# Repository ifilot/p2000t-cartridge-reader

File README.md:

# P2000T Cartridge Reader

This repository contains hard- and software utilities to read P2000T cartridges
using an [Arduino Leonardo](https://docs.arduino.cc/hardware/leonardo) board.
The repository is organized as follows. The [arduino](arduino) folder contains
the source code for the Arduino Leonardo. In the [kicad](kicad) folder the
files can be found for the arduino shield board. Finally, in the [script](scripts)
folder a number of Python scripts can be found interfacing with the Arduino
Leonardo board to dump cartridge roms to a file.

## Kicad scheme

## Uploading the firmware

Open the [Arduino IDE](https://www.arduino.cc/en/software) and open the file
`cartridge_reader_firmware.ino`. Verify that the source code can be correctly
compiled and upload it to the Arduino Leonardo. Next, proceed to the Python
files as found below. Test that the interface is functioning and then use
the `readrom.py` file to dump the cartridges.

## Python files

The following three Python files are provided to interface with the Arduino
Leonardo Board. To work with these files, you need to have the
[pyserial](https://pypi.org/project/pyserial/) package installed.

* [serialtest.py](scripts/serialtest.py): Tests whether Python can succesfully
  interface with the Arduino Leonardo and the cartridge reader firmware.
* [comparison_test.py](scripts/comparison_test.py): Tests whether the standard
  basic cartridge can be succesfully read. This requires one to have such a
  cartridge in their possession.
* [readrom.py](scripts/readrom.py): Dumps the contents of the cartridge in
  a `rom.bin` file. The `rom.bin` file is stored in the same folder as where
  this file resides.

## Logic table

In the table below, the interfacing of the Arduino pins to the signals on the
P2000T cartridge can be found. This interfacing scheme has been designed
around the documentation as found [here](https://www.philips-p2000t.nl/cartridges/basic-cartridge).
**It should be explicitly mentioned that the scheme as found in the Field Support
Manual is erroneous and has the CARSEL1 (CS1) and CARSEL2 (CS2) pins swapped.**

| BANK | D8 / A12B | D2 / ~CS1 | D3 / ~CS2 | A12  | A13  | ~CS  |
|------|-----------|-----------|-----------|------|------|------|
|`0x00`| HIGH      | LOW       | HIGH      | LOW  | LOW  | LOW  |
|`0x01`| LOW       | LOW       | HIGH      | HIGH | LOW  | LOW  |
|`0x02`| HIGH      | HIGH      | LOW       | LOW  | HIGH | LOW  |
|`0x03`| LOW       | HIGH      | LOW       | HIGH | HIGH | LOW  |
| N/A  | x         | HIGH      | HIGH      | x    | x    | HIGH |

## Bill of materials

* Arduino Leonardo
* 2x15 pin edge connector; pitch 3.96mm
* 74HCT4040N or similar

## Picture

## Licensing

* All source code, i.e. the [firmware](arduino/cartridge_reader_firmware) and the Python [scripts](scripts)
  are released under a [GPLv3 license](https://www.gnu.org/licenses/gpl-3.0.html).
* The hardware files to (re)produce the Arduino board are released under the 
  [CC BY-SA 4.0](https://creativecommons.org/licenses/by-sa/4.0/) license.

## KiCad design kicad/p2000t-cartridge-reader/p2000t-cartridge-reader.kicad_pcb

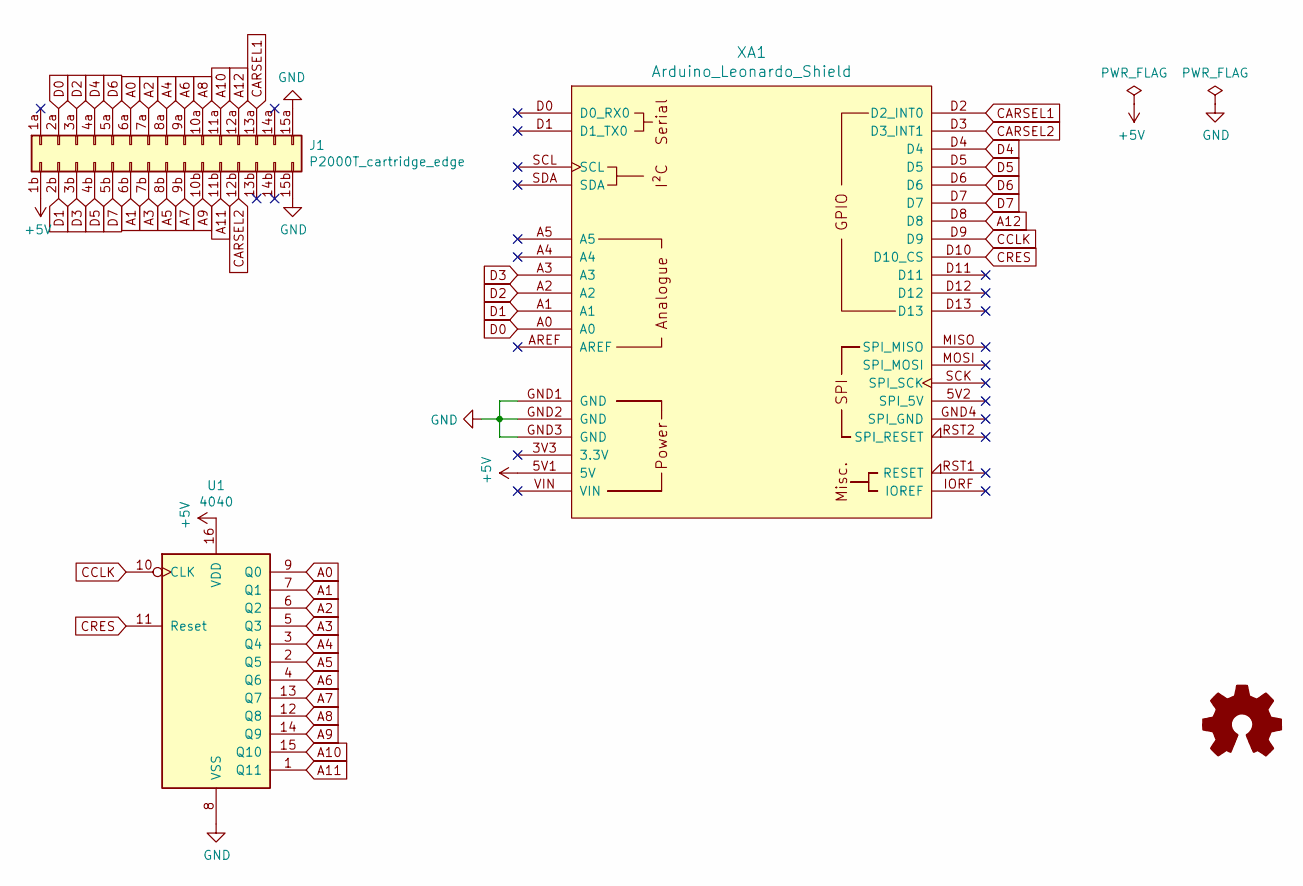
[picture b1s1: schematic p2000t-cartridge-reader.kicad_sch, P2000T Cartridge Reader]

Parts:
J1: P2000T_cartridge_edge; EdgeConnector2x15_no_screws
U1: 4040; DIP-16_W7.62mm_Socket
XA1: Arduino_Leonardo_Shield; Arduino_Uno_Shield

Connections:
+5V: J1.1b, U1.16 (VDD), XA1.5V1 (5V)
A0: J1.6a, U1.9 (Q0)
A1: J1.6b, U1.7 (Q1)
A2: J1.7a, U1.6 (Q2)
A3: J1.7b, U1.5 (Q3)
A4: J1.8a, U1.3 (Q4)
A5: J1.8b, U1.2 (Q5)
A6: J1.9a, U1.4 (Q6)
A7: J1.9b, U1.13 (Q7)
A8: J1.10a, U1.12 (Q8)
A9: J1.10b, U1.14 (Q9)
A10: J1.11a, U1.15 (Q10)
A11: J1.11b, U1.1 (Q11)
A12: J1.12a, XA1.D8
CARSEL1: J1.13a, XA1.D2 (D2_INT0)
CARSEL2: J1.12b, XA1.D3 (D3_INT1)
CCLK: U1.10 (CLK), XA1.D9
CRES: U1.11 (Reset), XA1.D10 (D10_CS)
D0: J1.2a, XA1.A0
D1: J1.2b, XA1.A1
D2: J1.3a, XA1.A2
D3: J1.3b, XA1.A3
D4: J1.4a, XA1.D4
D5: J1.4b, XA1.D5
D6: J1.5a, XA1.D6
D7: J1.5b, XA1.D7
GND: J1.15a, J1.15b, U1.8 (VSS), XA1.GND1 (GND), XA1.GND2 (GND), XA1.GND3 (GND)

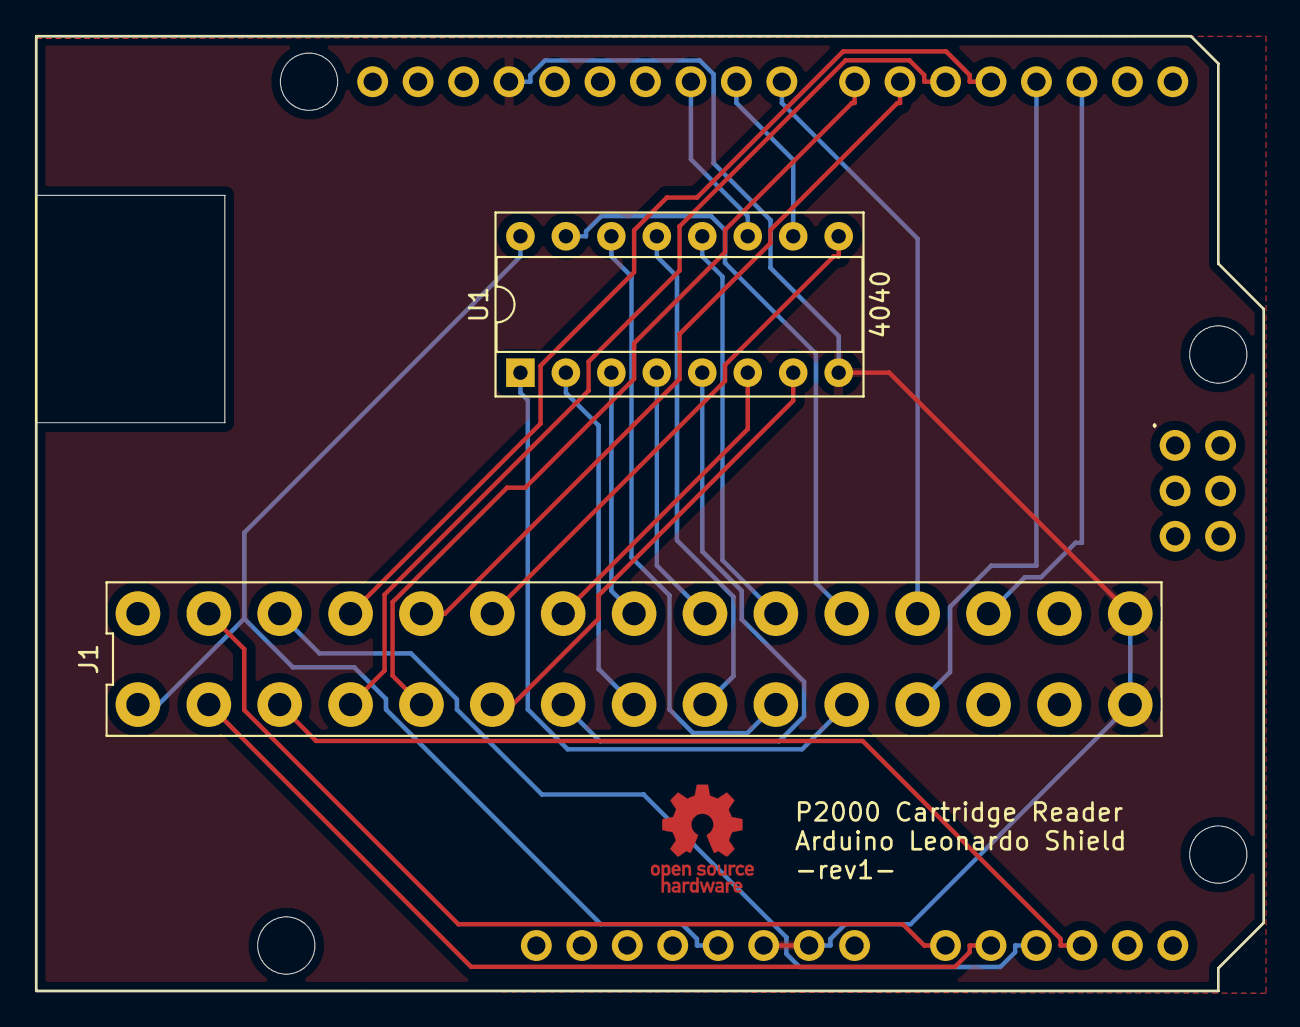
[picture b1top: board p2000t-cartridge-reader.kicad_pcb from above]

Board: 2 copper layers, 68.6 x 53.3 mm, 3 parts (0 on the bottom side), 27 nets.

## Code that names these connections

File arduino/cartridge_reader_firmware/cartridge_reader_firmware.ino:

/*
 * Note that there is an error in the Field Support Manual
 * 
 * CARSEL1 is on PIN 13A and CARSEL2 on PIN 12B; this is presented
 * reversed (incorrectly) in the FSM. See also:
 * https://www.philips-p2000t.nl/cartridges/basic-cartridge
 * 
 * Please note that this script only works for the P2000 Cartridge Reader
 * Boards __REV1__ and higher.
 */

#define ADDR_A12 8
#define ADDR_CARSEL1 2
#define ADDR_CARSEL2 3
#define CCLK 9
#define CRES 10

int lines[8] = {A0,A1,A2,A3,4,5,6,7};

// board identifier; this string needs to be 16 bytes long and terminated by a null character
char board_id[17] = {'P','2','k','0','_','V','1','.','0','.','0','_','_','_','_','_','\0'};

// global variables
char instruction[9];    // stores single 8-byte instruction
uint8_t inptr = 0;      // instruction pointer


void setup() {
  Serial.begin(115200);

  // set output on some pins
  pinMode(ADDR_A12, OUTPUT);
  pinMode(ADDR_CARSEL1, OUTPUT);
  pinMode(ADDR_CARSEL2, OUTPUT);
  pinMode(CCLK, OUTPUT);
  pinMode(CRES, OUTPUT);

  for(int i=0; i<8; i++) {
    pinMode(lines[i], INPUT);
  }

  // disable reset
  digitalWrite(CRES, LOW);
  digitalWrite(CCLK, HIGH);
}

uint8_t read_byte() {
  uint8_t val = 0;
  for(uint8_t i=0; i<8; i++) {
    val |= digitalRead(lines[i]) << i;
  }
  return val;
}

void set_address_start(uint16_t addr) {
  // reset counter
  digitalWrite(CRES, HIGH);
  digitalWrite(CRES, LOW);

  // read cartridge address
  bool a12 = bitRead(addr, 12);
  bool a13 = bitRead(addr, 13);
  uint8_t idx = a12 | (a13 << 1);

  // calculate load on cartridge lines
  static const bool a12p[4] = {HIGH,LOW,HIGH,LOW};
  static const bool cs1[4] = {LOW,LOW,HIGH,HIGH};
  static const bool cs2[4] = {HIGH,HIGH,LOW,LOW};

  // write to cartridge
  digitalWrite(ADDR_A12, a12p[idx]);
  digitalWrite(ADDR_CARSEL1, cs1[idx]);
  digitalWrite(ADDR_CARSEL2, cs2[idx]);
}

/*
 * Read block of 4096 bytes and output this
 * to the serial interface
 */
static void read_sector(uint16_t startaddress) {
  set_address_start(startaddress);
  for(int i=0; i<4096; i++) {
    Serial.write(read_byte());
    digitalWrite(CCLK, LOW);
    digitalWrite(CCLK, HIGH);
  }
}

/*
 * Capture address from last 6 bytes
 * of a command word
 */
static uint16_t get_addr_cmdword(const char* command) {
  char adrstr[7] = {'\0','\0','\0','\0','\0','\0','\0',};
  for(int i=0; i<6; i++) {
    adrstr[i] = command[i+2];
  }
  uint16_t saddr = strtoul(adrstr, NULL, 16);
  return saddr;
}

void loop() {
  if (Serial.available() > 0) {
    char c = Serial.read();

    // only capture alphanumerical data
    if((c >= 48 && c <= 57) || (c >= 65 && 90)) {
      instruction[inptr] = c;
      inptr++;
    }
  }

  // parse instruction
  if(inptr == 8) {
    // reset pointer
    inptr = 0;

    // interpret commands
    if(strcmp(instruction, "READINFO") == 0) {                    // read board id
      Serial.print(instruction);
      Serial.print(board_id);
    } else if(instruction[0] == 'R' && instruction[1] == 'B') {   // read sector
      Serial.print(instruction);
      uint16_t saddr = get_addr_cmdword(instruction);
      read_sector(saddr);
    }
  }
}

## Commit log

2023-07-04 Adding Kicad files
2023-07-04 Expanding README and adding requirements for Python
2023-07-04 Expanding README.md and adding images
2023-07-06 Improving find port function
2023-07-06 Fixing code in readrom function
2023-07-06 Adding license
2023-07-06 Updating licenses
